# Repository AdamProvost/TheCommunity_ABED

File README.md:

# TheCommunity_ABED

A.B.E.D == Automatic Breaking Emergency Device

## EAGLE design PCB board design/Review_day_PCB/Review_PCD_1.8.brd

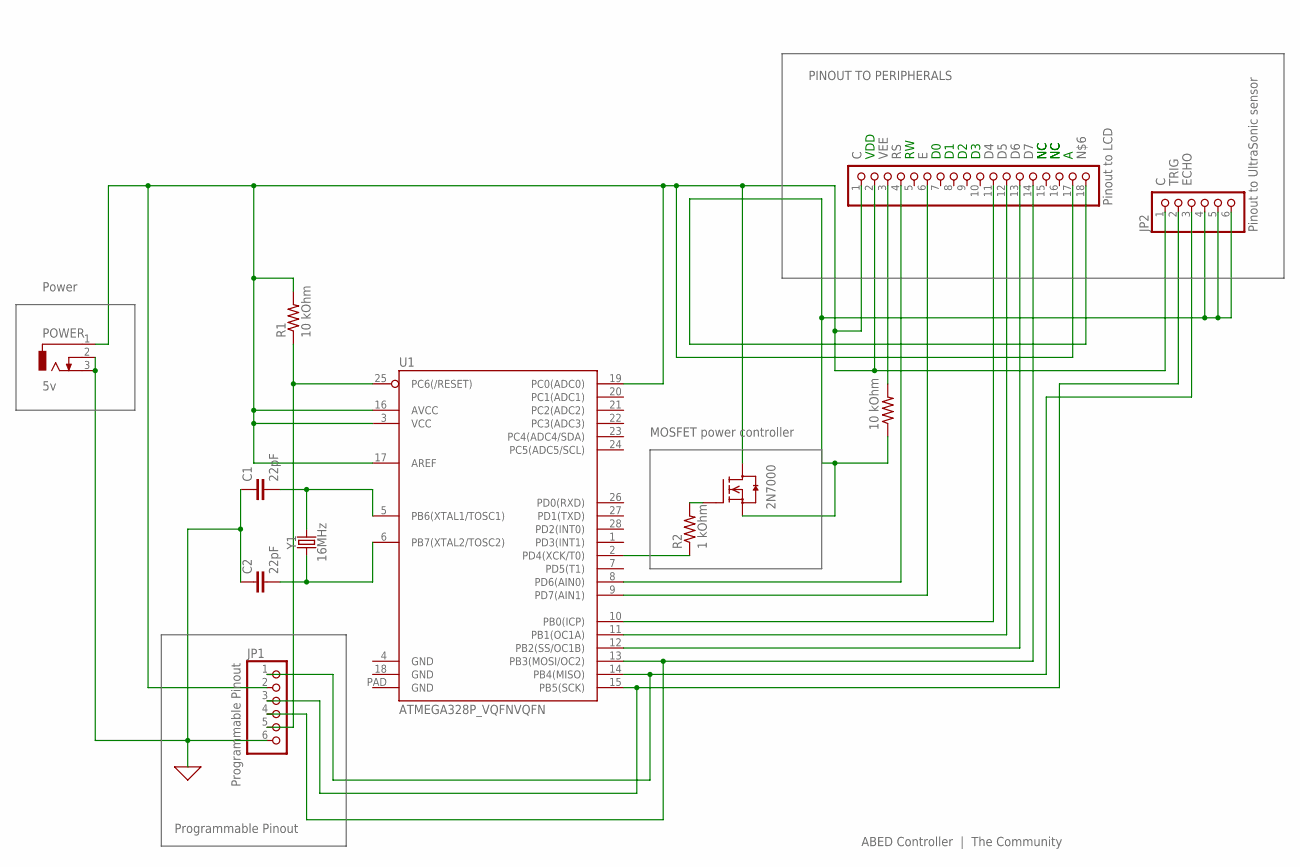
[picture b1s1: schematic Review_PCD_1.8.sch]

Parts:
C1, C2: 22pF; CAP-PTH-2.54
JP1: Programmable Pinout; 1X06-3.5MM
JP2: Pinout to UltraSonic sensor; 1X06-BIG
JP3: Pinout to LCD; 1X18
POWER: 5v; DCJ0202
Q2: 2N7000; TO92
R1, R3: 10 kOhm; R2012W
R2: 1 kOhm; R2012W
U1: ATMEGA328P_VQFNVQFN; VQFN-28
Y1: 16MHz; HC49US

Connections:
0: C1.1, C2.1, JP1.6, POWER.2, POWER.3
C: JP1.2, JP2.1, JP3.1, JP3.2, JP3.17, POWER.1, Q2.3 (D), R1.2, U1.3 (VCC), U1.16 (AVCC), U1.17 (AREF), U1.19 (PC0(ADC0))
D4: JP3.11, U1.10 (PB0(ICP))
D5: JP3.12, U1.11 (PB1(OC1A))
D6: JP3.13, U1.12 (PB2(SS/OC1B))
D7: JP1.4, JP3.14, U1.13 (PB3(MOSI/OC2))
E: JP3.6, U1.9 (PD7(AIN1))
ECHO: JP1.1, JP2.3, U1.14 (PB4(MISO))
unnamed: Q2.2 (G), R2.2
unnamed: JP1.5, R1.1, U1.25 (PC6(/RESET))
unnamed: R2.1, U1.2 (PD4(XCK/T0))
unnamed: C1.2, U1.5 (PB6(XTAL1/TOSC1)), Y1.2
unnamed: C2.2, U1.6 (PB7(XTAL2/TOSC2)), Y1.1
unnamed: JP2.4, JP2.5, JP2.6, JP3.18, Q2.1 (S), R3.1
RS: JP3.4, U1.8 (PD6(AIN0))
TRIG: JP1.3, JP2.2, U1.15 (PB5(SCK))
VEE: JP3.3, R3.2

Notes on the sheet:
VDD
PINOUT TO PERIPHERALS
ABED Controller | The Community
Programmable Pinout
Power
MOSFET power controller

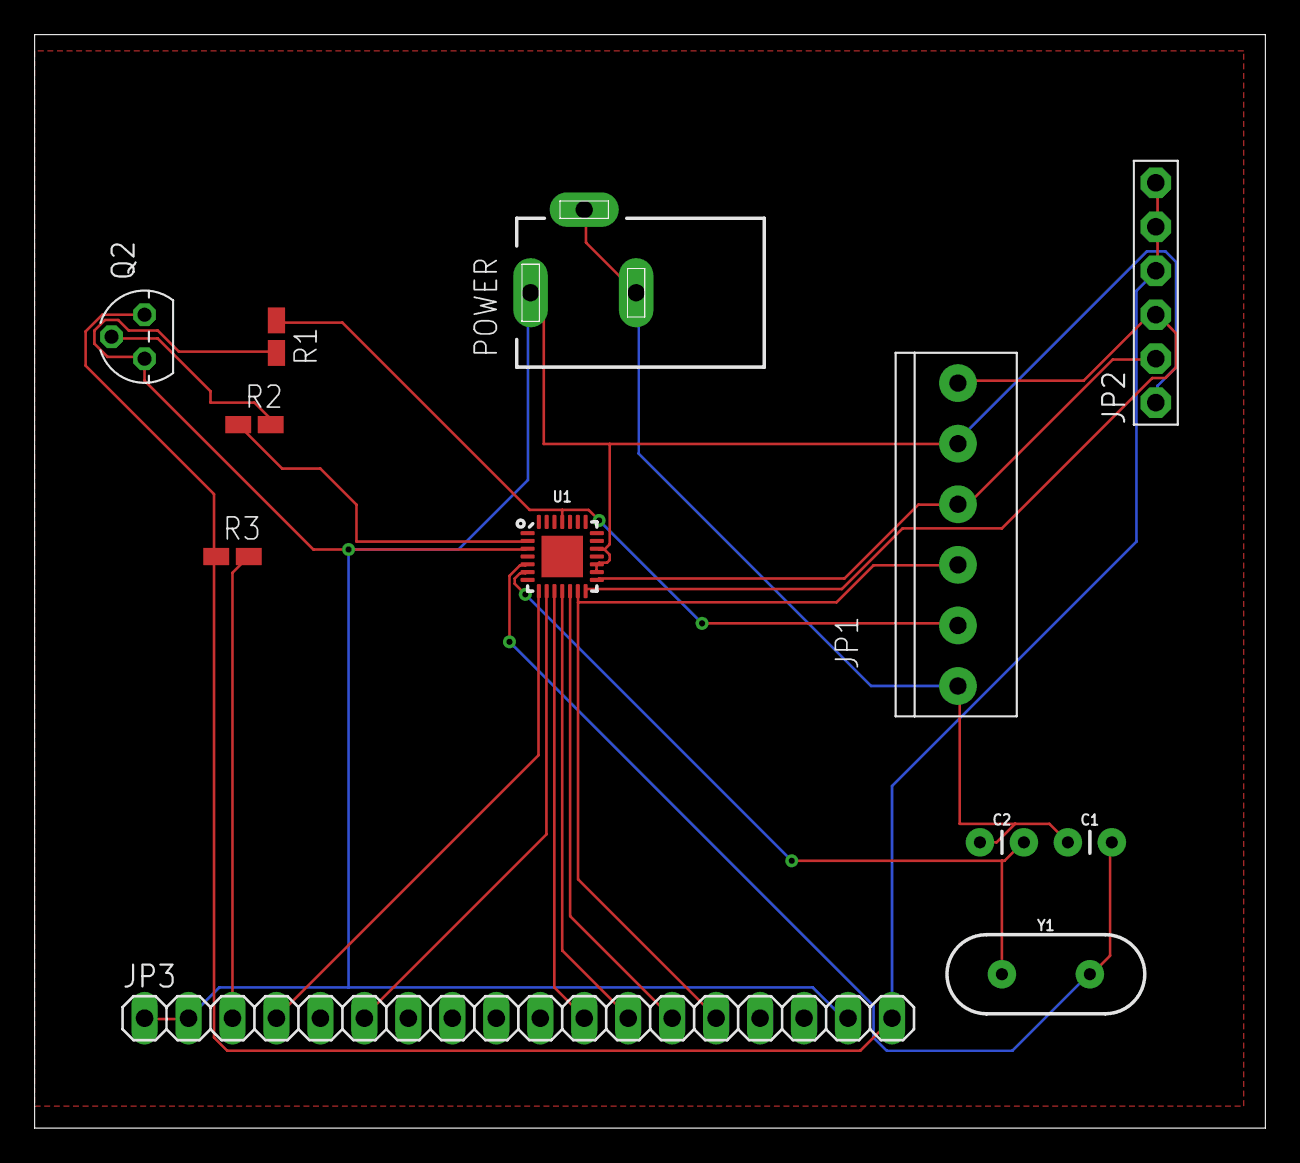
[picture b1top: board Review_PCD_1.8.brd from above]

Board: 2 copper layers, 71.1 x 63.2 mm, 12 parts (0 on the bottom side), 17 nets.

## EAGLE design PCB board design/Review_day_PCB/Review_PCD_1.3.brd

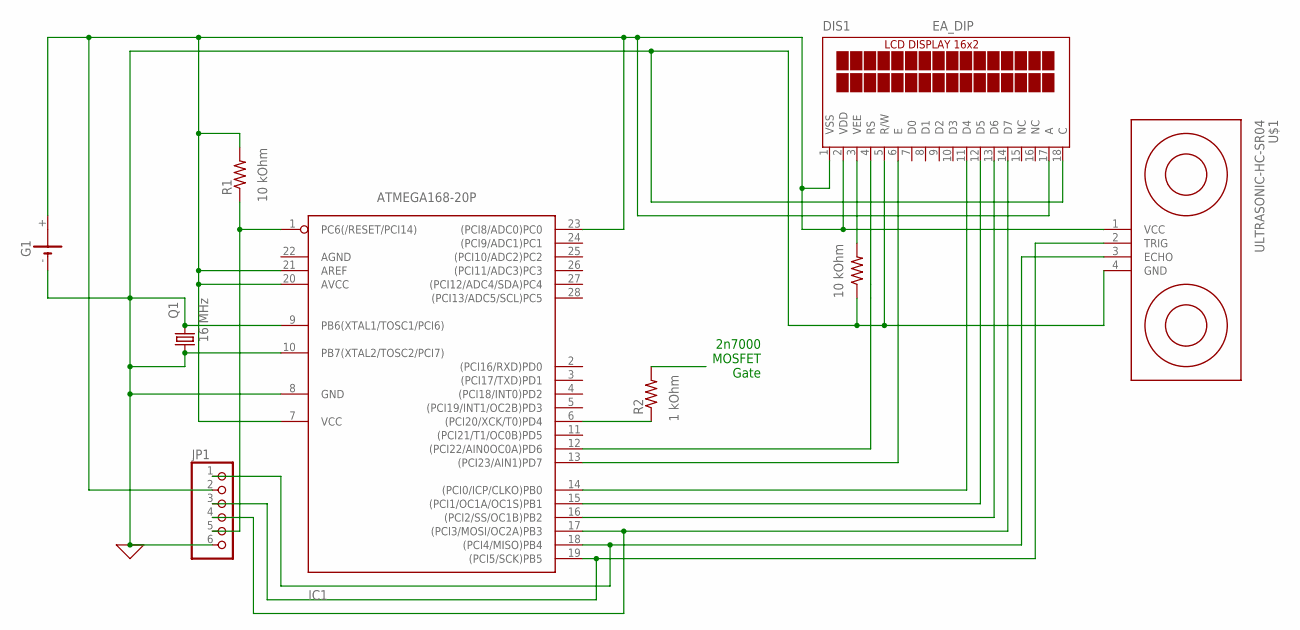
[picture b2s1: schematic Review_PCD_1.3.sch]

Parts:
DIS1: EA_DIP
G1: CR1/2
IC1: ATMEGA168-20P; DIL28-3
JP1: PINHD-1X6-3.5MM; 1X06-3.5MM
Q1: KX-4; 1.6X1.2
R1, R2, R3: R-US_R2012W; R2012W
U$1: ULTRASONIC-HC-SR04

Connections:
0: DIS1.5 (R/W), DIS1.18 (C), G1.-, IC1.8 (GND), IC1.9 (PB6(XTAL1/TOSC1/PCI6)), IC1.10 (PB7(XTAL2/TOSC2/PCI7)), JP1.6, Q1.1, Q1.3 (2), R3.1, U$1.4 (GND)
unnamed: DIS1.1 (VSS), DIS1.2 (VDD), DIS1.17 (A), G1.+, IC1.7 (VCC), IC1.20 (AVCC), IC1.21 (AREF), IC1.23 ((PCI8/ADC0)PC0), JP1.2, R1.2, U$1.1 (VCC)
unnamed: IC1.1 (PC6(/RESET/PCI14)), JP1.5, R1.1
unnamed: IC1.6 ((PCI20/XCK/T0)PD4), R2.1
unnamed: DIS1.4 (RS), IC1.12 ((PCI22/AIN0OC0A)PD6)
unnamed: DIS1.6 (E), IC1.13 ((PCI23/AIN1)PD7)
unnamed: DIS1.11 (D4), IC1.14 ((PCI0/ICP/CLKO)PB0)
unnamed: DIS1.12 (D5), IC1.15 ((PCI1/OC1A/OC1S)PB1)
unnamed: DIS1.13 (D6), IC1.16 ((PCI2/SS/OC1B)PB2)
unnamed: DIS1.3 (VEE), R3.2
unnamed: IC1.18 ((PCI4/MISO)PB4), JP1.1, U$1.3 (ECHO)
unnamed: IC1.19 ((PCI5/SCK)PB5), JP1.3, U$1.2 (TRIG)
unnamed: DIS1.14 (D7), IC1.17 ((PCI3/MOSI/OC2A)PB3), JP1.4

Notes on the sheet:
2n7000 MOSFET Gate

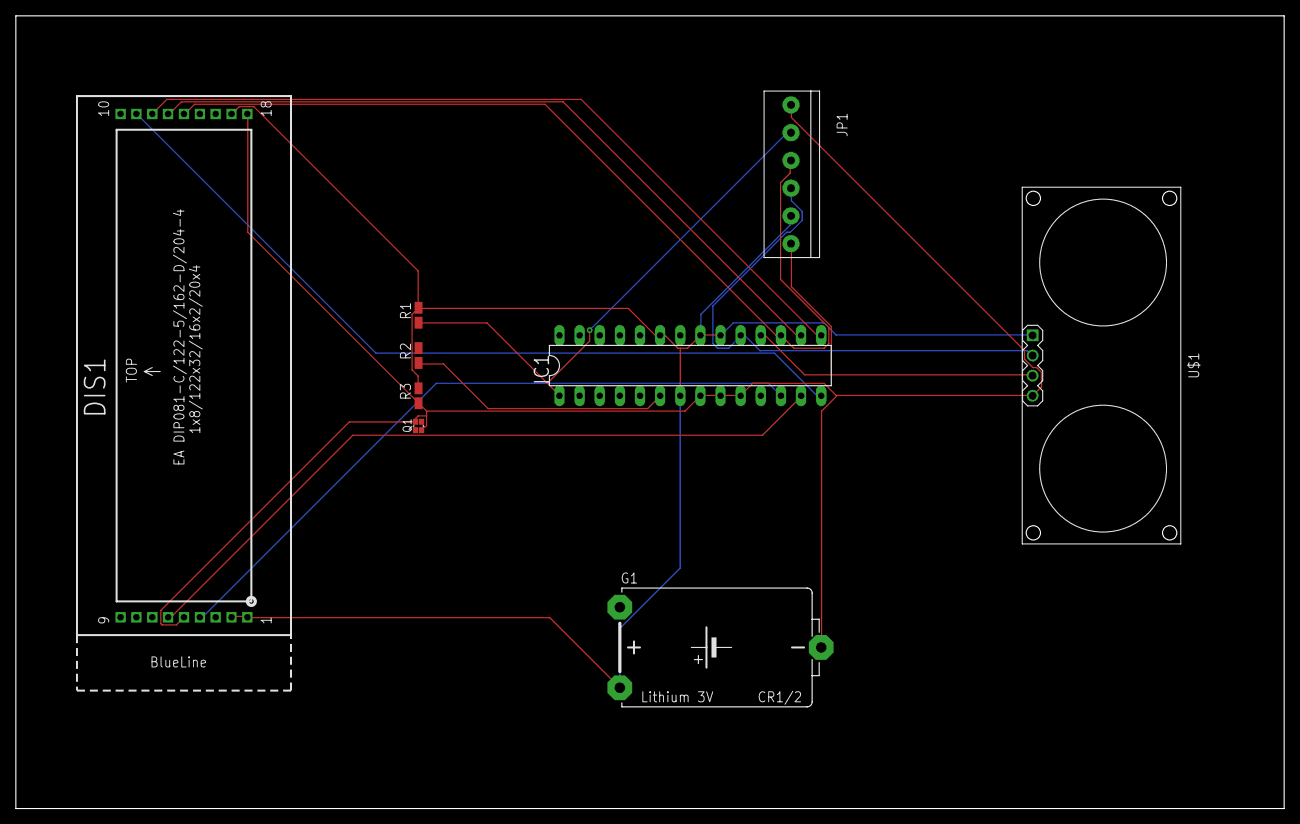
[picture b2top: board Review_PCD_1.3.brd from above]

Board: 2 copper layers, 160.0 x 100.0 mm, 9 parts (0 on the bottom side), 13 nets.

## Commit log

2020-10-13 edit
2020-10-13 new directory
2020-10-13 uploaded homework 2
2020-10-15 taking out old homework 2
2020-10-15 new homework
2020-10-15 .docx files dont show on github well
2020-10-15 hw2 edits
2020-10-22 adding hw 3
2020-10-23 updates to hw3
2020-10-25 Update to #3... level 1 schem
2020-10-25 Revsd HW2 formatting+names+grammar
2020-10-25 update pg 1 of hw3
2020-10-25 Rev 1.0 final rev? lots changed. gj everybody!
2020-10-25 Typo...
2020-10-26 Rev 1.2 - schematics and reqs.
2020-10-26 Design spec, rephrased sentences, and Typo fix
2020-10-26 Rev 1.3 Design spec, rephrased sentences, Typo fix
2020-10-26 Rev 1.3 Design spec, rephrased sentences/Typo
2020-10-26 fixed header & last name
2020-10-27 Create PCB board design
2020-10-30 breadbaord image
2020-11-02 Added Short Essay for "Bonus Points"
2020-11-05 Adding the Decision making HW pdf
2020-11-06 test code for baseline
2020-11-06 documentation
2020-11-06 directory README
2020-11-06 direction and documentation
2020-11-06 main.c
2020-11-06 main2.0
2020-11-06 main.2.0.ver2
2020-11-06 Working ABED-Controller Code in arduino sketch...
2020-11-07 Braking at 5cm... Need better Rb.
2020-11-07 update schematic also...
2020-11-08 Delete SampleBoard.sch
    Will upload it back with a correct name
2020-11-08 Add files via upload
    Uploading PCB Preliminary schematics
2020-11-08 Delete Schematic.sch
    Uploaded it with the correct name, Preliminary_PCB_1.0
    No longer needed
2020-11-09 Schem. with MOSFET/R4 and imprvd code prfmnc
2020-11-09 missed schematic. better code. delayed startup
2020-11-12 Updated load balancing and documents...
2020-11-13 BOM.xlsx
2020-11-13 BOM folder
2020-11-13 deletions
2020-11-13 new directory location with new file
2020-11-13 adding pdf version
2020-11-13 delete
2020-11-15 Uploading Preliminary PCB design Rev 1.3
2020-11-15 Removed two 10K resistors. Rev 1.4
2020-11-16 Updating schematic connections...
2020-11-16 rev.1.3
2020-11-16 schematic png
2020-11-17 changed to atmega328p
2020-11-17 all correct components and no errors
2020-11-17 complete schematic and layout
2020-11-18 organzied and optimized
2020-11-18 cleared fixable errors
2020-11-18 added planes
2020-11-18 navid saved the day
2020-11-19 PNGs
2020-11-19 Name Correction
2020-11-19 fixed ground planes
2020-11-26 state machine draft
2020-12-04 Images of Device on test vehicle
2020-12-04 Images of final board on test vehicle.
2020-12-05 Create Homework7
2020-12-09 testing auto-brake... works perfectly
2020-12-09 adding demo images/video

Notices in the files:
parts and their libraries:
crystal-geyer_V1_0: Copyright: Geyer-Electronic
diy-modules: Released under the Creative Commons Attribution 4.0 International License: http://creativecommons.org/licenses/by/4.0
m-pad-2.1: License : GNU General Public License version 2 (see bottom)
